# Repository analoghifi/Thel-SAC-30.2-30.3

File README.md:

# Thel SAC 30.2/30.3
Thel "**S**uper **A**ctive **C**rossover" (german: SA**W** 30.2/30.3) | 2-input ➔ 4-ouput | switchable: either 2-way-stereo or 3-way-mono | 24dB/Oct. Linkwitz-Riley  
realized as a 4th-order "state variable filter" according to:  
*>> Audio-Engineering-Society, Edition 1983 October 8-12, No. 2011 (B-2) by its inventor **Dennis A. Bohn**, Rane Corporation, Mountlake Terrace, Washington <<*  
➔ <a href="/docs/related/2099_AES_preprint_2011(B2)_1983.pdf">2099_AES_preprint_2011(B2)_1983.pdf</a>

maintaining a phase shift of 0° between the filter passes\* at any time at any frequency.  
*>>All in all, this results in perfect transmission in terms of time and level. The compromise is that the frequency-dependent phase rotation of this analogue filter is not shifted between the neighboring filter passes\*, but only between the input and output of the crossover.<<*  
  
\*(low-pass / band-pass / high-pass)   
<hr />

The original versions are equipped with balanced (symmetrical ) audio inputs  
but unbalanced (asymmetrical) audio outputs.
<hr />

In the <a href="/hardware">"hardware"</a> folder of this repository you can see the different versions of this module as they were built by THEL over the years and decades.  
This does NOT necessarily mean that the latest, newest version ("version 07.2017 until now") is also the "best" version.  
As you can see, in this case the sub-bass-boost feature and the extended supply voltage section is missing in the latest SAC 30.x  
and the very good PP 1% film/foil precision capacitors were switched to "normal" WIMA MKP 2.5% - 10% (or even MKS only).  
However, the latter in particular contradicts the goal of the 0° phase shift, because this requires that the determining filter capacitors and resistors have a tolerance of 1% or better (!).  
(In addition, the PP film/foil also sound better than the MKP types ➔ lower (and less frequency-dependent) dissipation factor "tan delta" etc...)  
On the other hand the latest, newest version ("version 07.2017 until now") introduces a much better input section (with 2 Op-Amps) in comparision to the previous model ("version 2011-2017")  
  
### So here is a comparison of this two versions and their specific pros and cons:  
#### Latest "<a href="/hardware/2)%20version%2007.2017%20until%20now">version 07.2017 until now</a>":  
:x: no "bass-boost" feature  
:x: using only "normal" capacitors in the filter section WIMA MKP 2.5% - 10% (or even worse: WIMA MKS)  
:x: no "Multi-Footprint" for the 8 filter capacitors (to optionally use different sizes and shapes of filter caps)  
:x: therefore no possibility to use the beloved tower style 1% precision KP film/foil caps in the filter section  
:x: no input caps in the power supply section  
:x: using of SOT-32 power transistors "only" in the power supply section (BD139/BD140 80V/1,5A/1,25W)  
:x: limited power supply voltage range of ±9V ... ±36V DC "only"  
:x: no possibility and space on the PCB to use optional (front panel mount) level potentiometers  
:x: no (RF-) bypass caps directly on the supply pins of the OP amps, although they are mandatory in every data sheet (for very good reasons)  
:heavy_check_mark: better audio input section with 2 OP-Amps (better symmetry / higher CMRR)   
:heavy_check_mark: using lower resistors in the filter section (less noise in theory)  
:heavy_check_mark: smaller dimensions (85 x 121mm)   
#### Previous "<a href="/hardware/3)%20version%202011-2017">version 2011-2017</a>":  
:heavy_check_mark: "bass-boost" feature  
:heavy_check_mark: using the high grade tower style 1% precision KP film/foil caps in the filter section  
:heavy_check_mark: "Multi-Footprint" for the 8 Filter capacitors to optionally use different sizes and shapes of filter caps  
:heavy_check_mark: 2 input caps (100µF) in the power supply section  
:heavy_check_mark: using of TO-220 power transistors in the power supply section (TIP132/TIP137 100V/8A/2,0W)  
:heavy_check_mark: extended power supply voltage range of ±9V ... ±60V DC  
:heavy_check_mark: preparation for using optional (front panel mount) level potentiometers directly on the PCB (in this case: TKD CP601 \[Conductive Plastic\])   
:x: no (RF-) bypass caps directly on the supply pins of the OP amps, although they are mandatory in every data sheet (for very good reasons)  
:x: using a simplified audio input section with 1 OP-Amp only (worse symmetry / lower CMRR)  
:x: using higher resistors in the filter section (more noise in theory)    
:x: larger dimensions (95 x 142mm)  
### my plans:  
* in the first step I will design a \"<a href="/hardware/1)%20my%20new%20version">new SAC30</a>\", which combines the advantages of the two versions mentioned above,  
it will still be in THT technology but 2 layer PCB, so that an average hobbyist can easily build it himself       
* the next step will be to create an all SMD version of this (eventually including 1% C0G ceramic filter caps), with some new features like symmetrical outputs, input/output ESD protection, ...)

<hr />  

## latest version as of 07.2017 until today:  

## better previous version (built 2011-2017):
   
using optional (front panel mount) level potentiometers directly on the PCB (in this case: TKD CP601 [Conductive Plastic]):   

https://web.archive.org/web/20071014012620/http://www.thel-audioworld.de/module/saw/saw.htm  
old frequency-table: https://web.archive.org/web/20160324050324/http://thel-audioworld.de/module/saw/SAWTAB.GIF  
https://web.archive.org/web/20110927050632/http://www.thel-audioworld.de/module/saw/saw.htm  
https://web.archive.org/web/20160406211449/http://www.thel-audioworld.de/MODULE/SAW/saw.htm  
https://web.archive.org/web/20180819222254/http://www.thel-audioworld.de/module/SAW/saw.htm  

----

----

here's a link to a calculation table (spreadsheet)  
to choose the right capacitors and resistors for a certain crossover frequency and to get the desired adjustment range:  
https://docs.google.com/spreadsheets/d/1a5ryznVy3UrqgniDteTX_oCJn4powWA7M3F-0194jWU/edit?usp=sharing

----  
### Kicad projects in this repo:  
* [version 2011-2017](https://github.com/analoghifi/Thel-SAC-30.2-30.3/tree/main/hardware/3\)%20version%202011-2017/KiCad/original) | state: initial release v1.01 | like the original, 1-layer, THT
* [version 07.2017 until now](https://github.com/analoghifi/Thel-SAC-30.2-30.3/tree/main/hardware/2\)%20version%2007.2017%20until%20now/KiCad/original) | state: initial release v1.01 | like the original, 1-layer, THT
* [my new version THT](https://github.com/analoghifi/Thel-SAC-30.2-30.3/tree/main/hardware/1\)%20my%20new%20version/KiCad/1.1\)%20my%20THT%20version) | state: coming soon... | 2-layer, THT
* [my new version SMD](https://github.com/analoghifi/Thel-SAC-30.2-30.3/tree/main/hardware/1\)%20my%20new%20version/KiCad/1.2\)%20my%20SMT%20version) | state: coming soon... | 2-layer, SMD

----

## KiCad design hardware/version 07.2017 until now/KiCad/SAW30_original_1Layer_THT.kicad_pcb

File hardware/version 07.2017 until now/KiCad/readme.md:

still a work in progress (PCB not finally finished yet)

these are KiCad 6.x projects  
see how to get the proper 3D-Models from here: https://github.com/analoghifi/KiCad-3D-Models

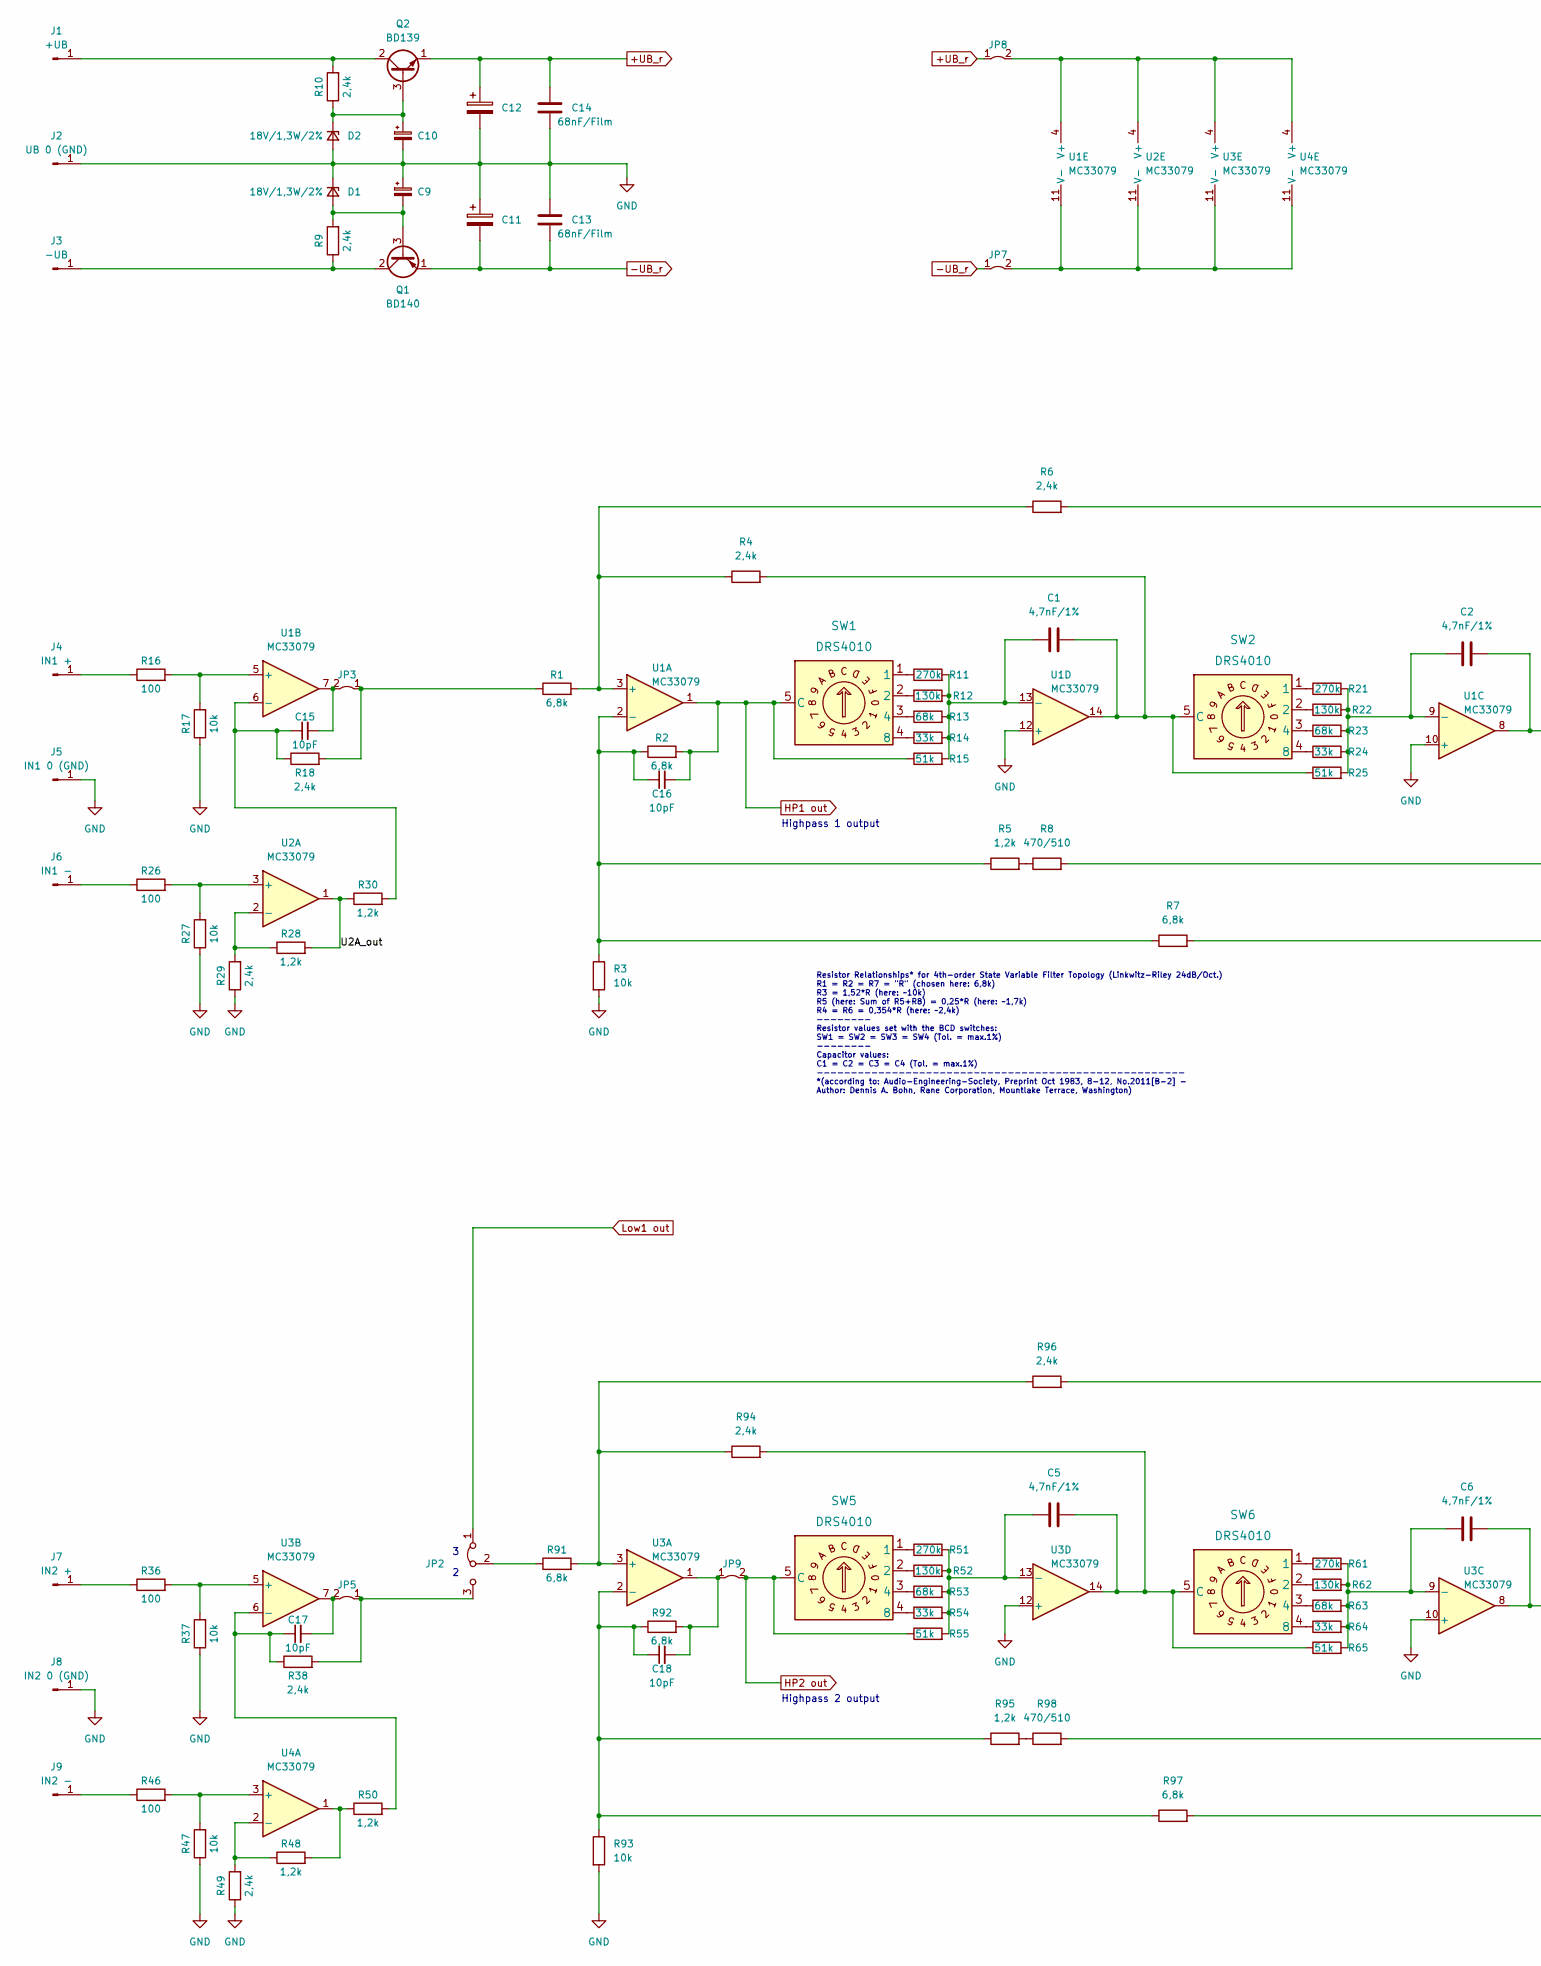
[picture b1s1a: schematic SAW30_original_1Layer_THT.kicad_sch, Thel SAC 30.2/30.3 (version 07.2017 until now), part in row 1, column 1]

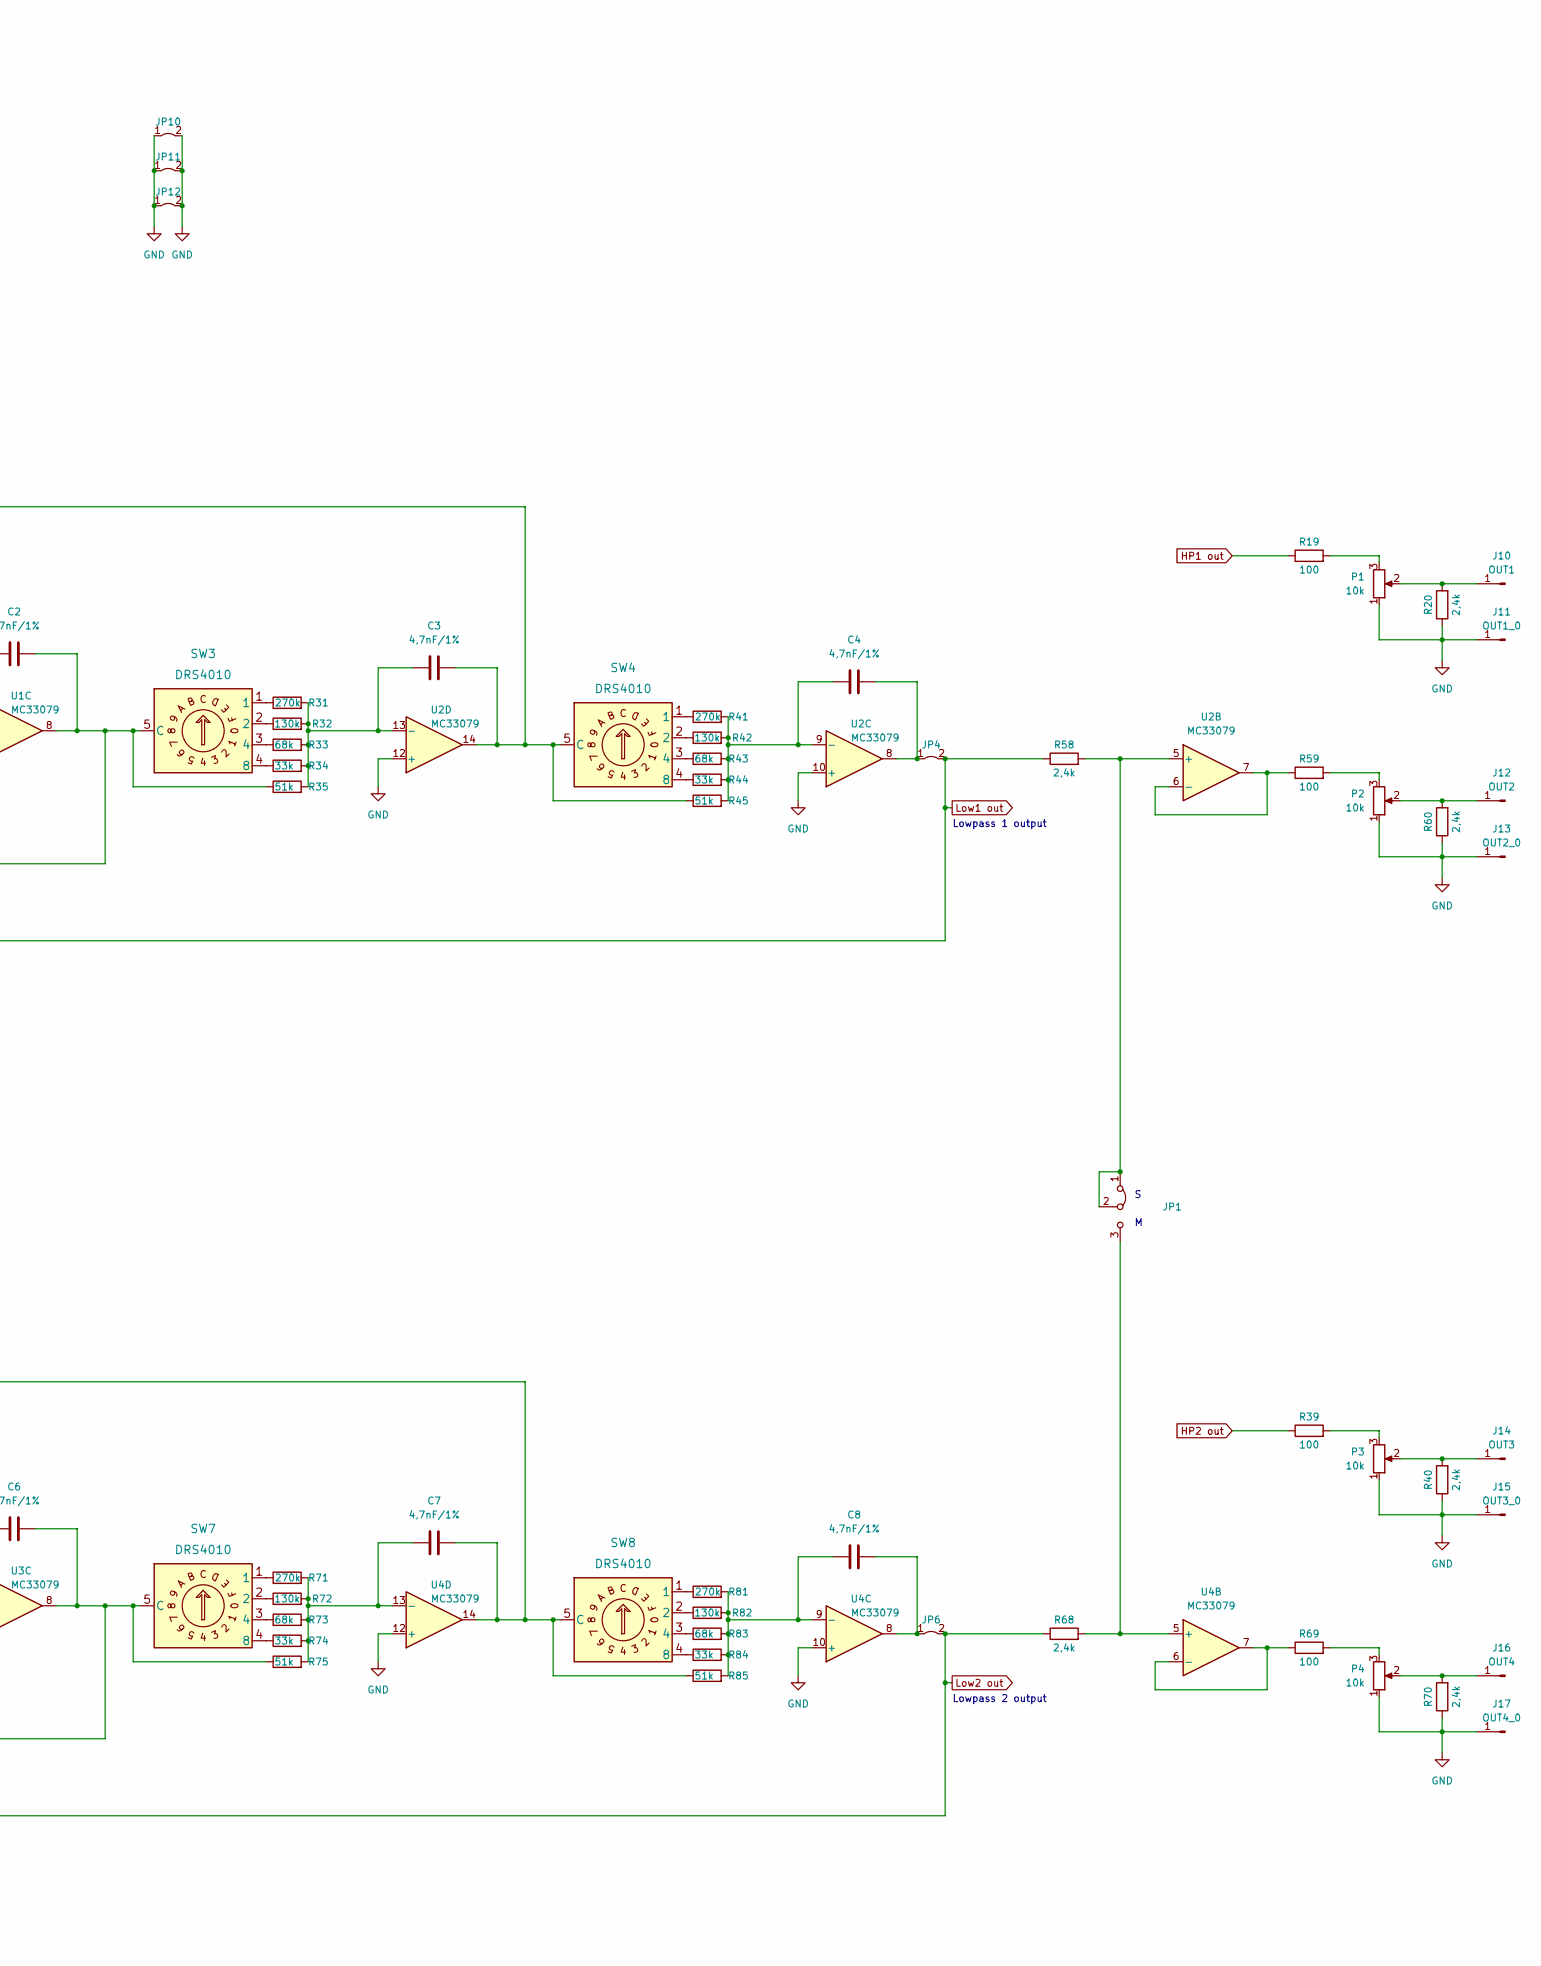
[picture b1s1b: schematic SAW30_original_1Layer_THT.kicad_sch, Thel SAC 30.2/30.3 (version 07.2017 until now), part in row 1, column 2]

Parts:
C1, C2, C3, C4, C5, C6, C7, C8: 4,7nF/1%; C_Rect_L10.0mm_W5.0mm_P5.00mm_P7.50mm
C9, C10, C11, C12: (no value)
C13, C14: 68nF/Film; C_Rect_L10.0mm_W5.0mm_P5.00mm_P7.50mm
C15, C16, C17, C18: 10pF; C_Rect_L4.0mm_W2.5mm_P2.50mm
D1, D2: 18V/1,3W/2%; D_DO-41_SOD81_P10.16mm_Horizontal_minSilk
J1: +UB; Loet_Pin_D1.5mm_L14.0mm
J2: UB 0 (GND); Loet_Pin_D1.5mm_L14.0mm
J3: -UB; Loet_Pin_D1.5mm_L14.0mm
J4: IN1 +; Loet_Pin_D1.5mm_L14.0mm
J5: IN1 0 (GND); Loet_Pin_D1.5mm_L14.0mm
J6: IN1 -; Loet_Pin_D1.5mm_L14.0mm
J7: IN2 +; Loet_Pin_D1.5mm_L14.0mm
J8: IN2 0 (GND); Loet_Pin_D1.5mm_L14.0mm
J9: IN2 -; Loet_Pin_D1.5mm_L14.0mm
J10: OUT1; Loet_Pin_D1.5mm_L14.0mm
J11: OUT1_0; Loet_Pin_D1.5mm_L14.0mm
J12: OUT2; Loet_Pin_D1.5mm_L14.0mm
J13: OUT2_0; Loet_Pin_D1.5mm_L14.0mm
J14: OUT3; Loet_Pin_D1.5mm_L14.0mm
J15: OUT3_0; Loet_Pin_D1.5mm_L14.0mm
J16: OUT4; Loet_Pin_D1.5mm_L14.0mm
J17: OUT4_0; Loet_Pin_D1.5mm_L14.0mm
JP1, JP2: Jumper_3_Bridged12; PinHeader_1x03_P2.54mm_Vertical
JP3, JP4, JP5, JP6, JP7, JP8, JP9, JP10, JP11, JP12: Jumper_2_Bridged; Drahtbruecke_10.16mm
P1, P2, P3, P4: 10k; Potentiometer_Bourns_3386P_Vertical
Q1: BD140; TO-126-3_Vertical
Q2: BD139; TO-126-3_Vertical
R1, R2, R7, R91, R92, R97: 6,8k; R_Axial_DIN0207_L6.3mm_D2.5mm_P10.16mm_Horizontal_minSilk
R3, R17, R27, R37, R47, R93: 10k; R_Axial_DIN0207_L6.3mm_D2.5mm_P10.16mm_Horizontal_minSilk
R4, R6, R9, R10, R18, R20, R29, R38, R40, R49, R58, R60, R68, R70, R94, R96: 2,4k; R_Axial_DIN0207_L6.3mm_D2.5mm_P10.16mm_Horizontal_minSilk
R5, R28, R30, R48, R50, R95: 1,2k; R_Axial_DIN0207_L6.3mm_D2.5mm_P10.16mm_Horizontal_minSilk
R8, R98: 470/510; R_Axial_DIN0207_L6.3mm_D2.5mm_P10.16mm_Horizontal_minSilk
R11, R21, R31, R41, R51, R61, R71, R81: 270k; R_Axial_DIN0207_L6.3mm_D2.5mm_P10.16mm_Horizontal_minSilk
R12, R22, R32, R42, R52, R62, R72, R82: 130k; R_Axial_DIN0207_L6.3mm_D2.5mm_P10.16mm_Horizontal_minSilk
R13, R23, R33, R43, R53, R63, R73, R83: 68k; R_Axial_DIN0207_L6.3mm_D2.5mm_P10.16mm_Horizontal_minSilk
R14, R24, R34, R44, R54, R64, R74, R84: 33k; R_Axial_DIN0207_L6.3mm_D2.5mm_P10.16mm_Horizontal_minSilk
R15, R25, R35, R45, R55, R65, R75, R85: 51k; R_Axial_DIN0207_L6.3mm_D2.5mm_P10.16mm_Horizontal_minSilk
R16, R19, R26, R36, R39, R46, R59, R69: 100; R_Axial_DIN0207_L6.3mm_D2.5mm_P10.16mm_Horizontal_minSilk
SW1, SW2, SW3, SW4, SW5, SW6, SW7, SW8: DRS4010; DRS_3016_4010
U1, U2, U3, U4: MC33079; DIP-14_W7.62mm

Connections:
+UB_r: C12.1, C14.1, JP8.1 (A), Q2.1 (E)
-UB_r: C11.2, C13.2, JP7.1 (A), Q1.1 (E)
/U2A_out: R28.2, R30.1, U2.1
GND: C9.1, C10.2, C11.1, C12.2, C13.1, C14.2, D1.1 (K), D2.2 (A), J2.1, J5.1, J8.1, J11.1, J13.1, J15.1, J17.1, JP10.1 (A), JP10.2 (B), JP11.1 (A), JP11.2 (B), JP12.1 (A), JP12.2 (B), P1.1, P2.1, P3.1, P4.1, R3.2, R17.1, R20.1, R27.1, R29.1, R37.1, R40.1, R47.1, R49.1, R60.1, R70.1, R93.2, U1.10 (+), U1.12 (+), U2.10 (+), U2.12 (+), U3.10 (+), U3.12 (+), U4.10 (+), U4.12 (+)
HP1 out: C16.2, R2.2, R15.1, R19.1, SW1.5 (C), U1.1
HP2 out: JP9.2 (B), R39.1, R55.1, SW5.5 (C)
Low1 out: JP2.1 (A), JP4.2 (B), R7.2, R58.1
Low2 out: JP6.2 (B), R68.1, R97.2
unnamed: C1.1, R11.2, R12.2, R13.2, R14.2, R15.2, U1.13 (-)
unnamed: C1.2, R4.2, R25.1, SW2.5 (C), U1.14
unnamed: C2.1, R21.2, R22.2, R23.2, R24.2, R25.2, U1.9 (-)
unnamed: C2.2, R8.2, R35.1, SW3.5 (C), U1.8
unnamed: C3.1, R31.2, R32.2, R33.2, R34.2, R35.2, U2.13 (-)
unnamed: C3.2, R6.2, R45.1, SW4.5 (C), U2.14
unnamed: C4.1, R41.2, R42.2, R43.2, R44.2, R45.2, U2.9 (-)
unnamed: C4.2, JP4.1 (A), U2.8
unnamed: C5.1, R51.2, R52.2, R53.2, R54.2, R55.2, U3.13 (-)
unnamed: C5.2, R65.1, R94.2, SW6.5 (C), U3.14
unnamed: C6.1, R61.2, R62.2, R63.2, R64.2, R65.2, U3.9 (-)
unnamed: C6.2, R75.1, R98.2, SW7.5 (C), U3.8
unnamed: C7.1, R71.2, R72.2, R73.2, R74.2, R75.2, U4.13 (-)
unnamed: C7.2, R85.1, R96.2, SW8.5 (C), U4.14
unnamed: C8.1, R81.2, R82.2, R83.2, R84.2, R85.2, U4.9 (-)
unnamed: C8.2, JP6.1 (A), U4.8
unnamed: C9.2, D1.2 (A), Q1.3 (B), R9.2
unnamed: C10.1, D2.1 (K), Q2.3 (B), R10.1
unnamed: C15.1, R18.1, R30.2, U1.6 (-)
unnamed: C15.2, JP3.2 (B), U1.7
unnamed: C16.1, R2.1, R3.1, R5.1, R7.1, U1.2 (-)
unnamed: C17.1, R38.1, R50.2, U3.6 (-)
unnamed: C17.2, JP5.2 (B), U3.7
unnamed: C18.1, R92.1, R93.1, R95.1, R97.1, U3.2 (-)
unnamed: C18.2, JP9.1 (A), R92.2, U3.1
unnamed: J1.1, Q2.2 (C), R10.2
unnamed: J3.1, Q1.2 (C), R9.1
unnamed: J4.1, R16.1
unnamed: J6.1, R26.1
unnamed: J7.1, R36.1
unnamed: J9.1, R46.1
unnamed: J10.1, P1.2, R20.2
unnamed: J12.1, P2.2, R60.2
unnamed: J14.1, P3.2, R40.2
unnamed: J16.1, P4.2, R70.2
unnamed: JP1.1 (A), JP1.2 (C), R58.2, U2.5 (+)
unnamed: JP1.3 (B), R68.2, U4.5 (+)
unnamed: JP2.2 (C), R91.1
unnamed: JP2.3 (B), JP5.1 (A), R38.2
unnamed: JP3.1 (A), R1.1, R18.2
unnamed: JP7.2 (B), U1.11 (V-), U2.11 (V-), U3.11 (V-), U4.11 (V-)
unnamed: JP8.2 (B), U1.4 (V+), U2.4 (V+), U3.4 (V+), U4.4 (V+)
unnamed: P1.3, R19.2
unnamed: P2.3, R59.2
unnamed: P3.3, R39.2
unnamed: P4.3, R69.2
unnamed: R1.2, R4.1, R6.1, U1.3 (+)
unnamed: R5.2, R8.1
unnamed: R11.1, SW1.1
unnamed: R12.1, SW1.2
unnamed: R13.1, SW1.3 (4)
unnamed: R14.1, SW1.4 (8)
unnamed: R21.1, SW2.1
unnamed: R22.1, SW2.2
unnamed: R23.1, SW2.3 (4)
unnamed: R24.1, SW2.4 (8)
unnamed: R31.1, SW3.1
unnamed: R32.1, SW3.2
unnamed: R33.1, SW3.3 (4)
unnamed: R34.1, SW3.4 (8)
unnamed: R41.1, SW4.1
unnamed: R42.1, SW4.2
unnamed: R43.1, SW4.3 (4)
unnamed: R44.1, SW4.4 (8)
unnamed: R51.1, SW5.1
unnamed: R52.1, SW5.2
unnamed: R53.1, SW5.3 (4)
unnamed: R54.1, SW5.4 (8)
unnamed: R61.1, SW6.1
unnamed: R62.1, SW6.2
unnamed: R63.1, SW6.3 (4)
unnamed: R64.1, SW6.4 (8)
unnamed: R71.1, SW7.1
unnamed: R72.1, SW7.2
unnamed: R73.1, SW7.3 (4)
unnamed: R74.1, SW7.4 (8)
unnamed: R81.1, SW8.1
unnamed: R82.1, SW8.2
unnamed: R83.1, SW8.3 (4)
unnamed: R84.1, SW8.4 (8)
unnamed: R95.2, R98.1
unnamed: R91.2, R94.1, R96.1, U3.3 (+)
unnamed: R16.2, R17.2, U1.5 (+)
unnamed: R28.1, R29.2, U2.2 (-)
unnamed: R26.2, R27.2, U2.3 (+)
unnamed: R59.1, U2.6 (-), U2.7
unnamed: R36.2, R37.2, U3.5 (+)
unnamed: R48.2, R50.1, U4.1
unnamed: R48.1, R49.2, U4.2 (-)
unnamed: R46.2, R47.2, U4.3 (+)
unnamed: R69.1, U4.6 (-), U4.7

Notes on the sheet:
Lowpass 2 output
Highpass 2 output
Lowpass 1 output
Resistor Relationships* for 4th-order State Variable Filter Topology (Linkwitz-Riley 24dB/Oct.) R1 = R2 = R7 = "R" (chosen here: 6,8k) R3 = 1,52*R (here: ~10k) R5 (here: Sum of R5+R8) = 0,25*R (here: ~1,7k) R4 = R6 = 0,354*R (here: ~2,4k) -------- Resistor values set with the BCD switches: SW1 = SW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
Highpass 1 output

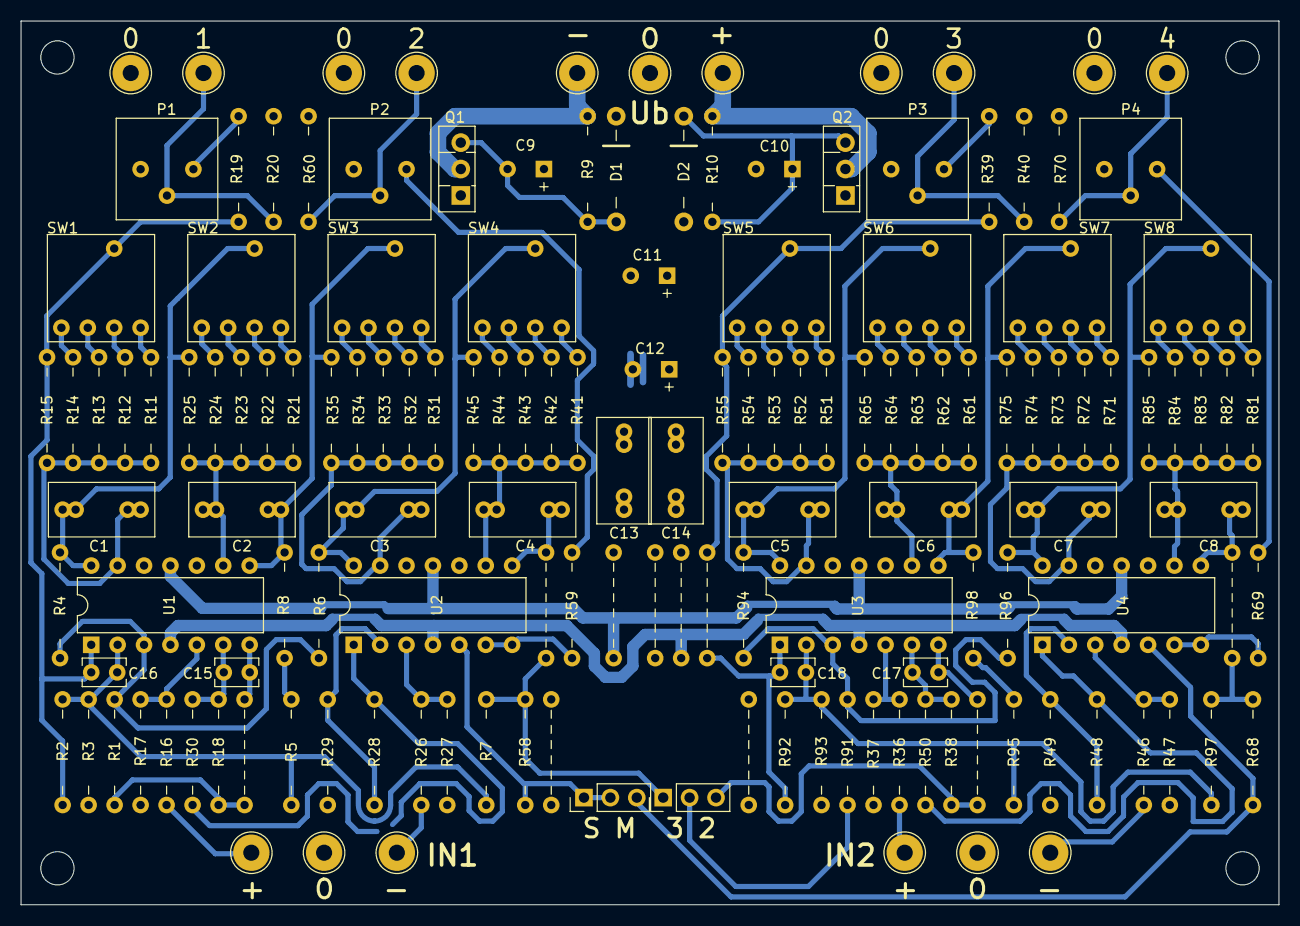
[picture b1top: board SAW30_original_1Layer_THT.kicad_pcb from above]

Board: 2 copper layers, 121.0 x 85.0 mm, 151 parts (0 on the bottom side), 99 nets.

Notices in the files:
parts and their libraries:
Copyright 2021 Accelerated Designs. All rights reserved.
